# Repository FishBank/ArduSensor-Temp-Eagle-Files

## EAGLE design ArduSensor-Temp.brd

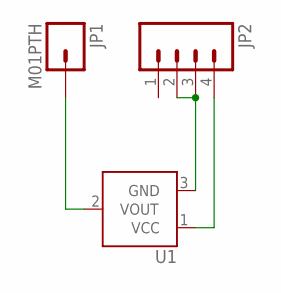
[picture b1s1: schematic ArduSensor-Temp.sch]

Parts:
JP1: M01PTH; 1X01
JP2: M04PTH; 1X04
U1: TMP36GT9; TO-92

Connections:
unnamed: JP1.1, U1.2 (VOUT)
unnamed: JP2.2, JP2.3, U1.3 (GND)
unnamed: JP2.4, U1.1 (VCC)

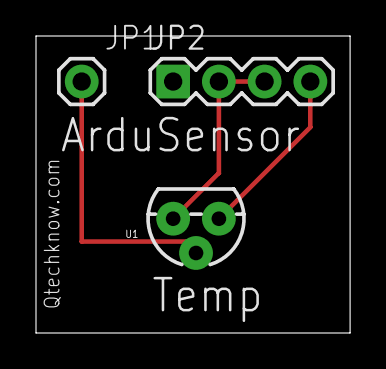
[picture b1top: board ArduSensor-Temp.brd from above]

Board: 2 copper layers, 17.4 x 16.5 mm, 3 parts (0 on the bottom side), 3 nets.

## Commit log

2012-07-13 Schematic

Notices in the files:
parts and their libraries:
SFE Sensors: Licensing: CC v3.0 Share-Alike You are welcome to use this library for commercial purposes.
